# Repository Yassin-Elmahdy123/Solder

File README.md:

# schematic circuit:

# PCB circuit:

# 3D circuit:

# Describtion:
### This is my hand made circuit. It consists of two LEDs, two resistors, two push buttons, and a battery holder. When the two push buttons are pressed, the two LEDs turn on. When the left push button is pressed, the left LED turns on. However, when the right push button is pressed, no LED turns on. It'a my first time to make a PCB and i will call it (BOB).

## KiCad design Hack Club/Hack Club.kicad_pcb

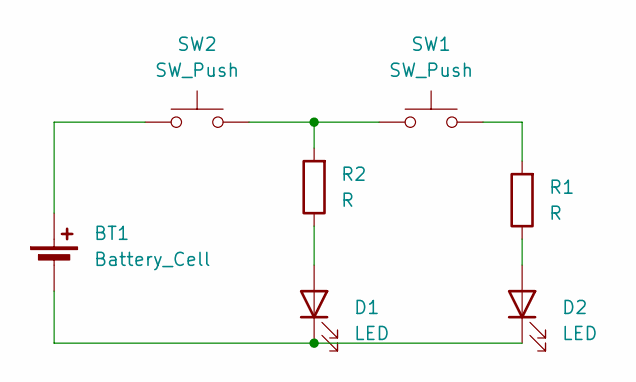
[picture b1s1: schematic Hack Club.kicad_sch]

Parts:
BT1: Battery_Cell; BatteryHolder_Keystone_3034_1x20mm
D1, D2: LED; LED_D5.0mm
R1, R2: R; R_Axial_DIN0207_L6.3mm_D2.5mm_P7.62mm_Horizontal
SW1, SW2: SW_Push; SW_PUSH_6mm_H7.3mm

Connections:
unnamed: BT1.1 (+), SW2.1
unnamed: BT1.2 (-), D1.1 (K), D2.1 (K)
unnamed: D1.2 (A), R2.1
unnamed: D2.2 (A), R1.1
unnamed: R1.2, SW1.2
unnamed: R2.2, SW1.1, SW2.2

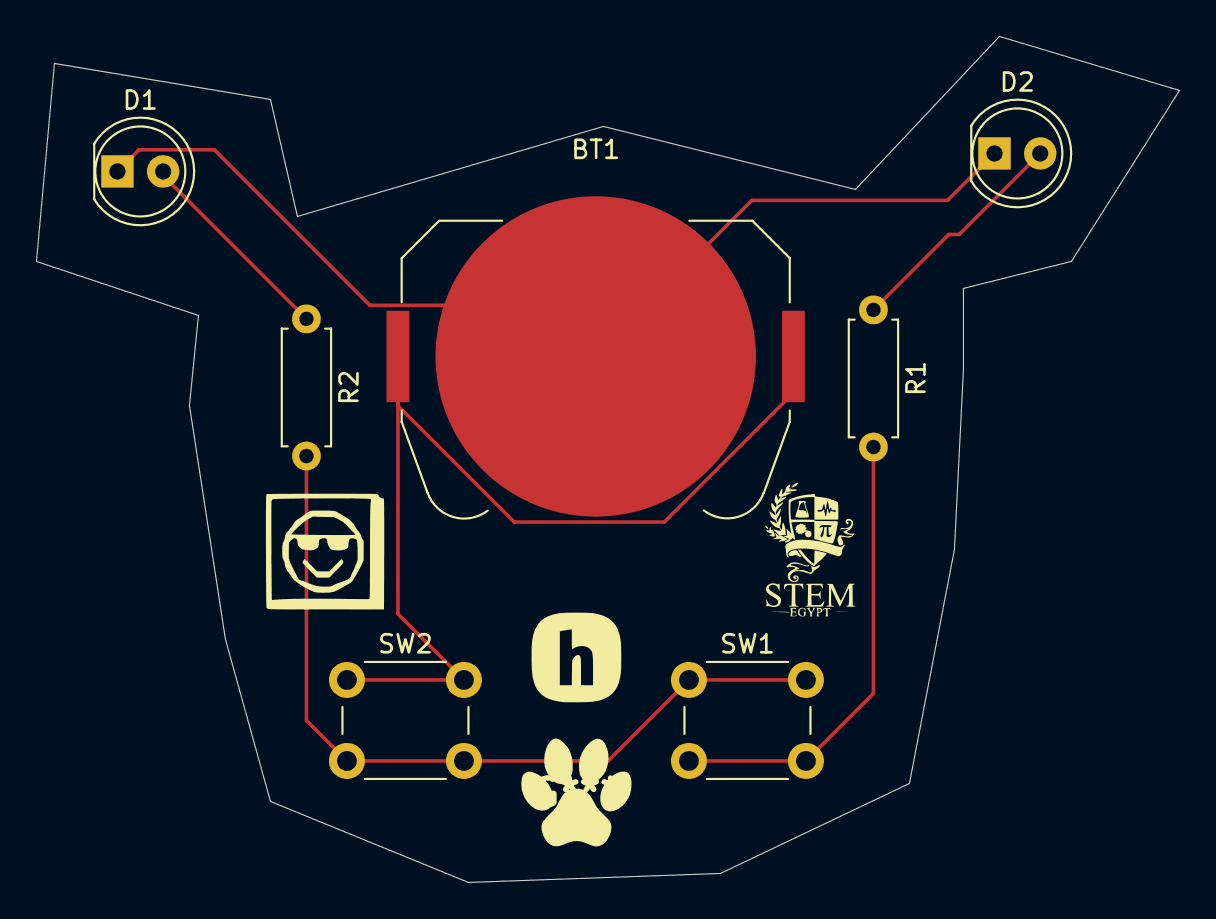
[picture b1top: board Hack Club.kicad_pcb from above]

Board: 2 copper layers, 63.5 x 47.0 mm, 7 parts (0 on the bottom side), 6 nets.
